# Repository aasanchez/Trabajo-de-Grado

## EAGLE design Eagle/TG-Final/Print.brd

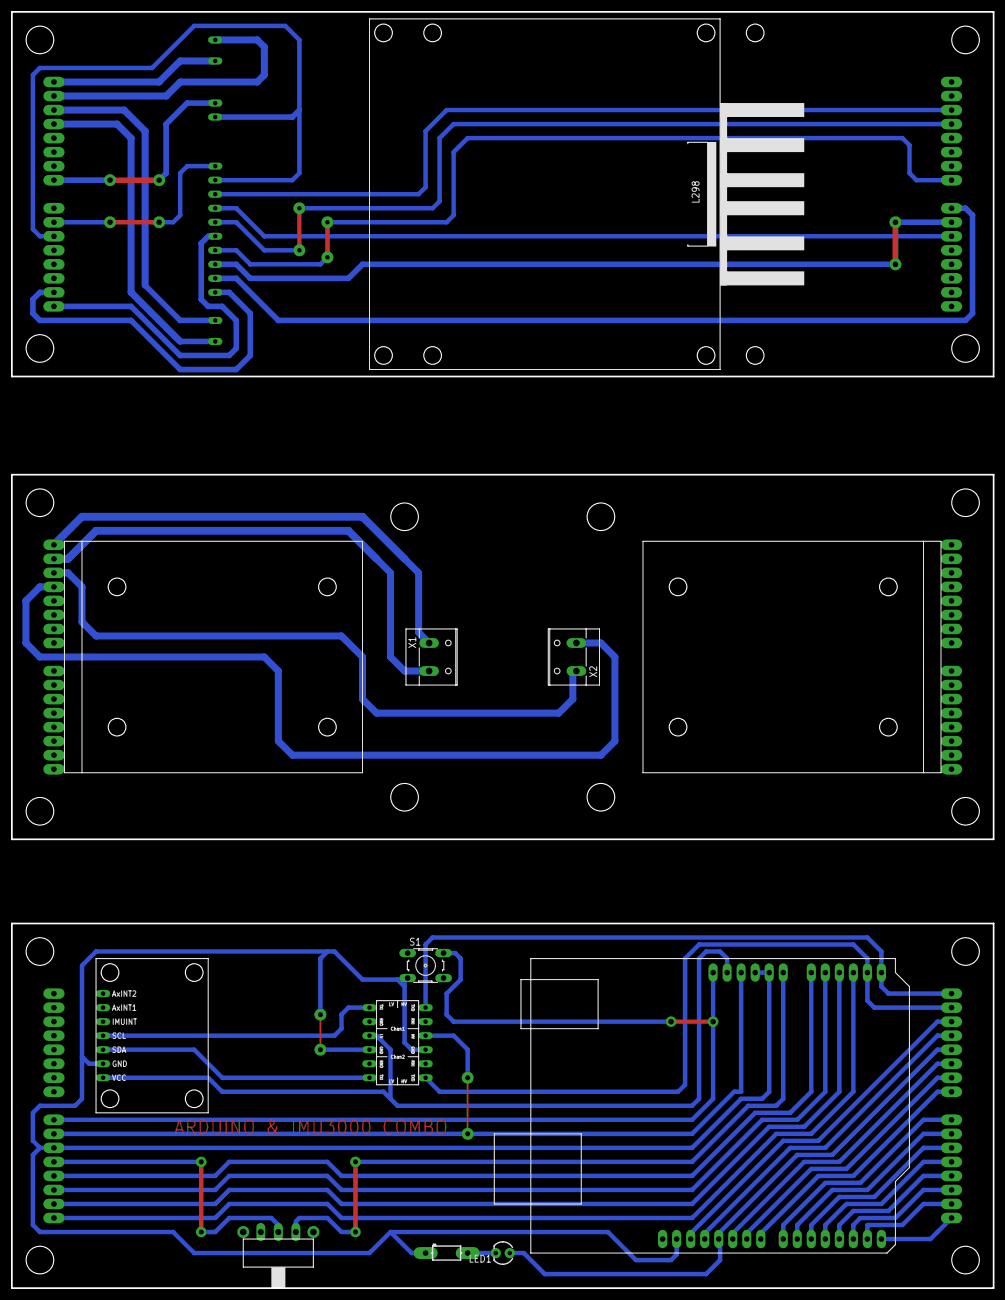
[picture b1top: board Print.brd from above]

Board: 2 copper layers, 177.8 x 231.1 mm, 15 parts (1 on the bottom side), 48 nets.

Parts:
LED1: LED3MM
R1: AXIAL-0.3-KIT
S1: B3F-10XX
S2: TL39YOSWITCH_2_ESTADOS; TL3XYO
U$1, U$2, U$5: BASE-FINAL
U$3, U$4: BASEMOTOR
U$6: ARDUINO-NOHOLE
U$7: IMU3000COMBO; IMU3000-COMBO
U$8: LOGIC-LEVEL-CONVERTER; LEVEL-CONVERTER
U$9: UK1122FINO; UK1122-2
X1, X2: W237-132

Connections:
5V: U$1.5V, U$6.5V, U$8.P$10
+3V3: U$6.3V, U$7.3V3, U$8.P$3
A0: U$1.A0, U$6.A0
A1: U$1.A1, U$6.A1
A2: U$1.A2, U$6.A2
A3: U$1.A3, U$6.A3
A4: U$1.A4, U$6.A4, U$8.P$7
A5: U$1.A5, U$6.A5, U$8.P$12
CSB: U$5.A2, U$9.CSB
GND: R1.P$1, S1.3, U$1.GND, U$6.GND, U$6.GND1, U$6.GND2, U$7.VSS, U$8.P$4, U$8.P$9
IN4: U$5.7, U$9.IN4
MOT2A: U$5.PIN03, U$9.MOT2A
MOT2R: U$5.PIN02, U$9.MOT2R
unnamed: U$7.SCL, U$8.P$1
unnamed: U$7.SDA, U$8.P$6
unnamed: S2.2, U$1.VIN
unnamed: U$2.PIN01, X1.2
unnamed: U$2.PIN02, X2.1
unnamed: U$2.PIN03, X2.2
unnamed: U$2.PIN00, X1.1
unnamed: U$5.PIN00, U$9.MOT1A
unnamed: U$5.PIN01, U$9.MOT1R
unnamed: U$5.5V, U$9.GND
unnamed: U$5.13, U$9.IN1
unnamed: U$5.12, U$9.EN2
unnamed: U$5.5, U$9.ENA
unnamed: U$5.A3, U$9.CSA
unnamed: U$5.8, U$9.IN3
unnamed: U$5.6, U$9.ENB
unnamed: U$5.12V, U$9.+
unnamed: U$5.GND, U$9.+5, U$9.-
unnamed: LED1.K, R1.P$2
PIN16: U$1.0, U$6.D0
PIN17: U$1.1, U$6.D1
PIN18: U$1.2, U$6.D2
PIN19: U$1.3, U$6.D3
PIN20: U$1.4, U$6.D4
PIN21: U$1.5, U$6.D5
PIN22: U$1.6, U$6.D6
PIN23: U$1.7, U$6.D7
PIN24: U$1.8, U$6.D8
PIN25: U$1.9, U$6.D9
PIN26: U$1.10, U$6.D10
PIN27: LED1.A, U$1.11, U$6.D11
PIN28: U$1.12, U$6.D12
PIN29: U$1.13, U$6.D13
RST: S1.2, U$1.RST, U$6.RESET
VIN: S2.1, U$6.VIN

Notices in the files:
parts and their libraries:
SparkFun: Licensing: CC v3.0 Share-Alike You are welcome to use this library for commercial purposes.
